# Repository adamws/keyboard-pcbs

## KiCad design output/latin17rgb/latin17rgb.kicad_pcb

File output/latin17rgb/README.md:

## latin17rgb/latin17rgb

[layout](latin17rgb-kle.json) - [PCB](latin17rgb.kicad_pcb)

{:loading="lazy"}

[Open in keyboard-layout-editor](http://www.keyboard-layout-editor.com/##@@=0,0&=0,1&=0,2&=0,3;&@=1,0&=1,1&=1,2&_h:2;&=1,3;&@=2,0&=2,1&=2,2;&@=3,0&=3,1&=3,2&_h:2;&=3,3;&@_w:2;&=4,0&=4,1)

{:loading="lazy"}

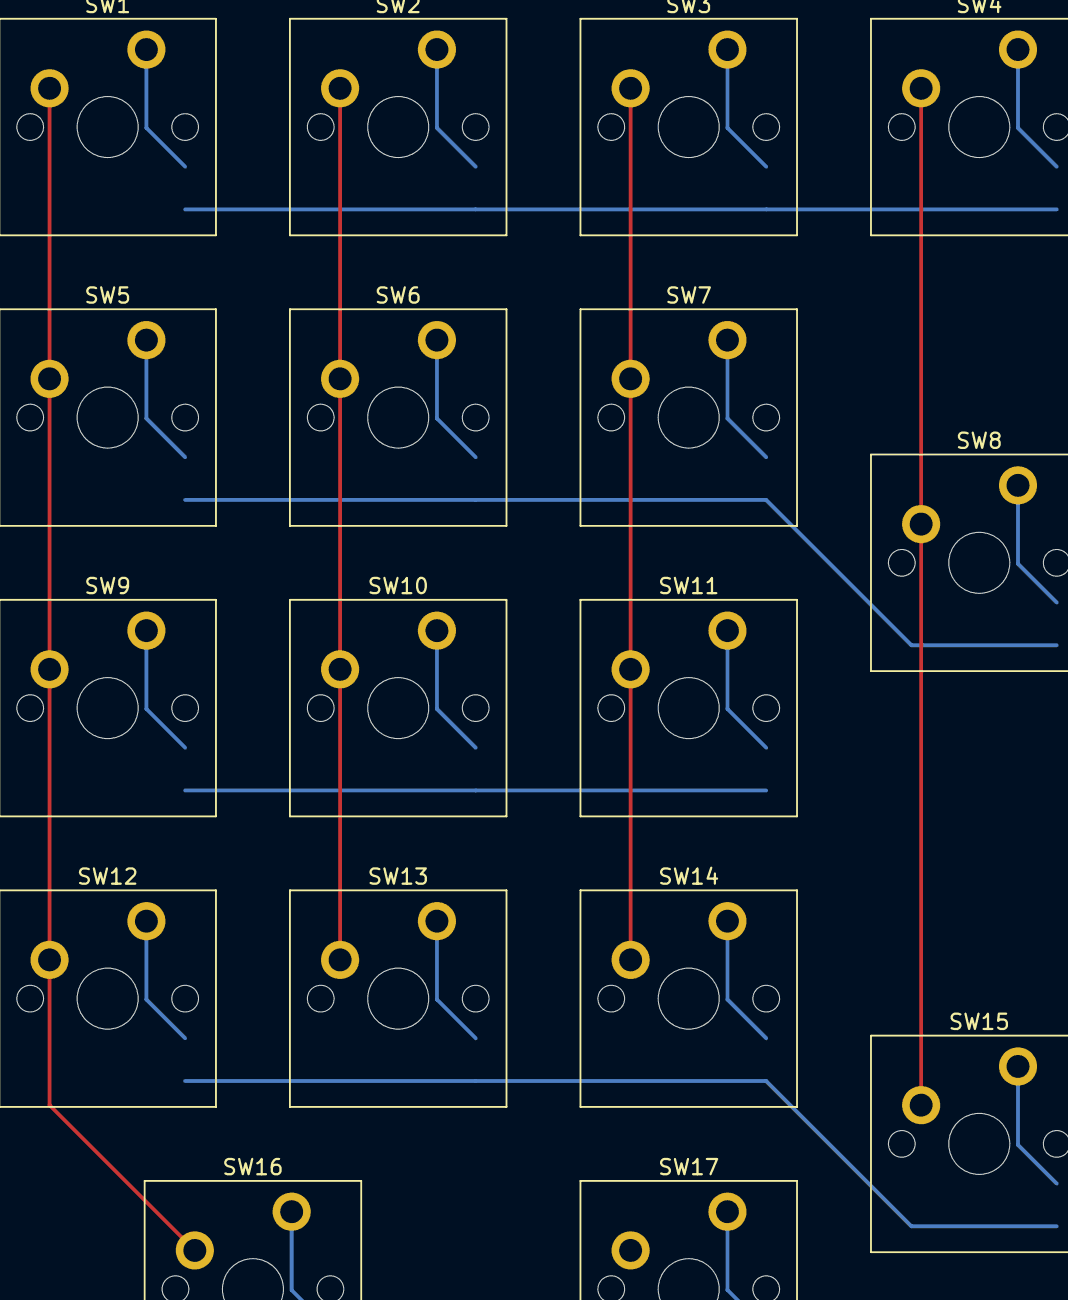
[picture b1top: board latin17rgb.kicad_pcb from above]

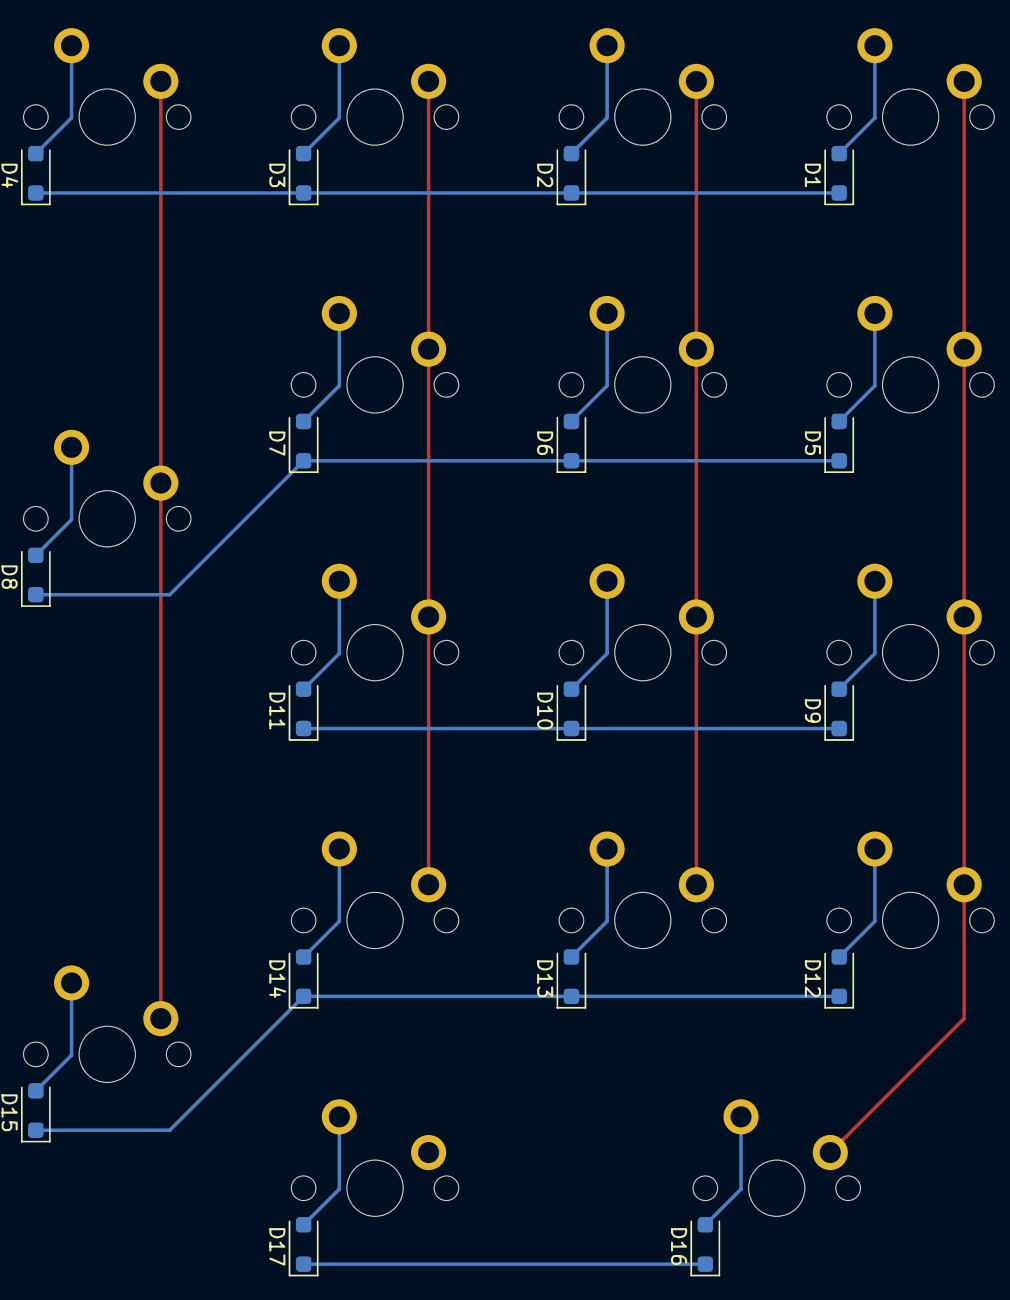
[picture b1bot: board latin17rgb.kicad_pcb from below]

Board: 2 copper layers, 34 parts (17 on the bottom side), 26 nets.

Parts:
D1, D2, D3, D4, D5, D6, D7, D8, D9, D10, D11, D12, D13, D14, D15, D16, D17: D_SOD-123F
SW1, SW2, SW3, SW4, SW5, SW6, SW7, SW8, SW9, SW10, SW11, SW12, SW13, SW14, SW15, SW16, SW17: SW_Cherry_MX_PCB_1.00u

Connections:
COL0: SW1.1, SW5.1, SW9.1, SW12.1, SW16.1
COL1: SW2.1, SW6.1, SW10.1, SW13.1, SW17.1
COL2: SW3.1, SW7.1, SW11.1, SW14.1
COL3: SW4.1, SW8.1, SW15.1
unnamed: D1.2, SW1.2
unnamed: D2.2, SW2.2
unnamed: D3.2, SW3.2
unnamed: D4.2, SW4.2
unnamed: D5.2, SW5.2
unnamed: D6.2, SW6.2
unnamed: D7.2, SW7.2
unnamed: D8.2, SW8.2
unnamed: D9.2, SW9.2
unnamed: D10.2, SW10.2
unnamed: D11.2, SW11.2
unnamed: D12.2, SW12.2
unnamed: D13.2, SW13.2
unnamed: D14.2, SW14.2
unnamed: D15.2, SW15.2
unnamed: D16.2, SW16.2
unnamed: D17.2, SW17.2
ROW0: D1.1, D2.1, D3.1, D4.1
ROW1: D5.1, D6.1, D7.1, D8.1
ROW2: D9.1, D10.1, D11.1
ROW3: D12.1, D13.1, D14.1, D15.1
ROW4: D16.1, D17.1

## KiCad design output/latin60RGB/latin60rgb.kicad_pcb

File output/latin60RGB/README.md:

## latin60RGB/latin60rgb

[layout](latin60rgb-kle.json) - [PCB](latin60rgb.kicad_pcb)

{:loading="lazy"}

[Open in keyboard-layout-editor](http://www.keyboard-layout-editor.com/##@@=0,0&=0,1&=0,2&=0,3&=0,4&=0,5&=0,6&=0,7&=0,8&=0,9&=0,10&=0,11&=0,12&_w:2;&=0,13;&@_w:1.5;&=1,0&=1,1&=1,2&=1,3&=1,4&=1,5&=1,6&=1,7&=1,8&=1,9&=1,10&=1,11&=1,12&_w:1.5;&=1,13;&@_w:1.75;&=2,0&=2,1&=2,2&=2,3&=2,4&=2,5&=2,6&=2,7&=2,8&=2,9&=2,10&=2,11&_w:2.25;&=2,12;&@_w:2;&=3,0&=3,1&=3,2&=3,3&=3,4&=3,5&=3,6&=3,7&=3,8&=3,9&=3,10&=3,11&=3,12&=3,13;&@_x:1.25&w:1.25;&=4,0&_w:1.25;&=4,1&_w:6.25;&=4,2&_w:1.25;&=4,3&_w:1.25;&=4,4)

{:loading="lazy"}

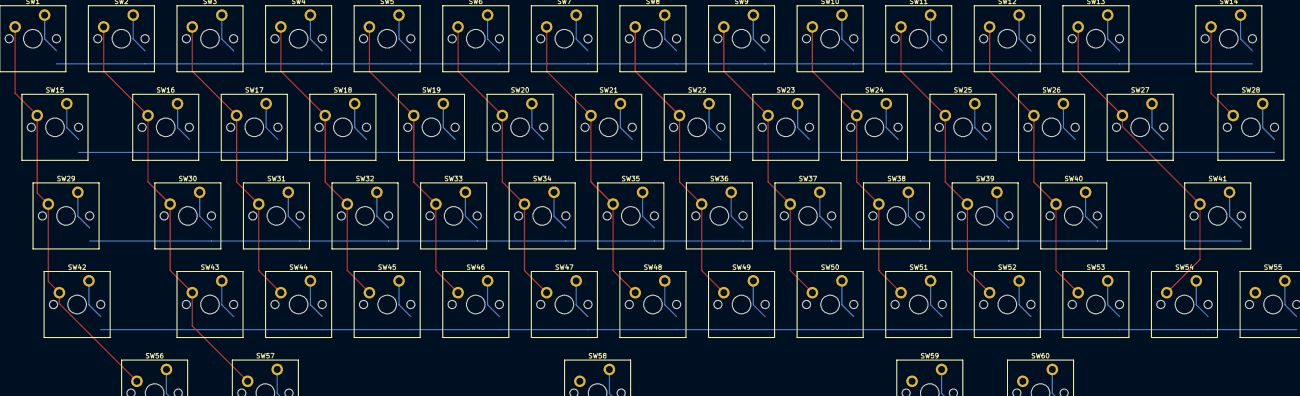
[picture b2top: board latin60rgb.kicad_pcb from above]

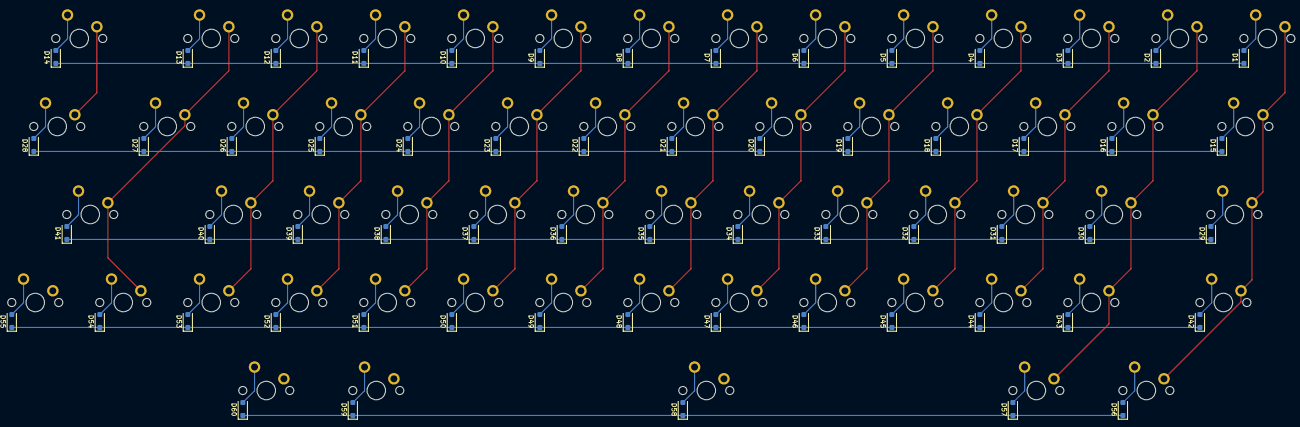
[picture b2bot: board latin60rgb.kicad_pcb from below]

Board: 2 copper layers, 120 parts (60 on the bottom side), 79 nets.

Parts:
D1, D2, D3, D4, D5, D6, D7, D8, D9, D10, D11, D12, D13, D14, D15, D16, D17, D18, D19, D20, D21, D22, D23, D24, D25, D26, D27, D28, D29, D30, D31, D32, D33, D34, D35, D36, D37, D38, D39, D40, D41, D42, D43, D44, D45, D46, D47, D48, D49, D50, D51, D52, D53, D54, D55, D56, D57, D58, D59, D60: D_SOD-123F
SW1, SW2, SW3, SW4, SW5, SW6, SW7, SW8, SW9, SW10, SW11, SW12, SW13, SW14, SW15, SW16, SW17, SW18, SW19, SW20, SW21, SW22, SW23, SW24, SW25, SW26, SW27, SW28, SW29, SW30, SW31, SW32, SW33, SW34, SW35, SW36, SW37, SW38, SW39, SW40, SW41, SW42, SW43, SW44, SW45, SW46, SW47, SW48, SW49, SW50, SW51, SW52, SW53, SW54, SW55, SW56, SW57, SW58, SW59, SW60: SW_Cherry_MX_PCB_1.00u

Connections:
COL0: SW1.1, SW15.1, SW29.1, SW42.1, SW56.1
COL1: SW2.1, SW16.1, SW30.1, SW43.1, SW57.1
COL2: SW3.1, SW17.1, SW31.1, SW44.1, SW58.1
COL3: SW4.1, SW18.1, SW32.1, SW45.1, SW59.1
COL4: SW5.1, SW19.1, SW33.1, SW46.1, SW60.1
COL5: SW6.1, SW20.1, SW34.1, SW47.1
COL6: SW7.1, SW21.1, SW35.1, SW48.1
COL7: SW8.1, SW22.1, SW36.1, SW49.1
COL8: SW9.1, SW23.1, SW37.1, SW50.1
COL9: SW10.1, SW24.1, SW38.1, SW51.1
COL10: SW11.1, SW25.1, SW39.1, SW52.1
COL11: SW12.1, SW26.1, SW40.1, SW53.1
COL12: SW13.1, SW27.1, SW41.1, SW54.1
COL13: SW14.1, SW28.1, SW55.1
unnamed: D1.2, SW1.2
unnamed: D2.2, SW2.2
unnamed: D3.2, SW3.2
unnamed: D4.2, SW4.2
unnamed: D5.2, SW5.2
unnamed: D6.2, SW6.2
unnamed: D7.2, SW7.2
unnamed: D8.2, SW8.2
unnamed: D9.2, SW9.2
unnamed: D10.2, SW10.2
unnamed: D11.2, SW11.2
unnamed: D12.2, SW12.2
unnamed: D13.2, SW13.2
unnamed: D14.2, SW14.2
unnamed: D15.2, SW15.2
unnamed: D16.2, SW16.2
unnamed: D17.2, SW17.2
unnamed: D18.2, SW18.2
unnamed: D19.2, SW19.2
unnamed: D20.2, SW20.2
unnamed: D21.2, SW21.2
unnamed: D22.2, SW22.2
unnamed: D23.2, SW23.2
unnamed: D24.2, SW24.2
unnamed: D25.2, SW25.2
unnamed: D26.2, SW26.2
unnamed: D27.2, SW27.2
unnamed: D28.2, SW28.2
unnamed: D29.2, SW29.2
unnamed: D30.2, SW30.2
unnamed: D31.2, SW31.2
unnamed: D32.2, SW32.2
unnamed: D33.2, SW33.2
unnamed: D34.2, SW34.2
unnamed: D35.2, SW35.2
unnamed: D36.2, SW36.2
unnamed: D37.2, SW37.2
unnamed: D38.2, SW38.2
unnamed: D39.2, SW39.2
unnamed: D40.2, SW40.2
unnamed: D41.2, SW41.2
unnamed: D42.2, SW42.2
unnamed: D43.2, SW43.2
unnamed: D44.2, SW44.2
unnamed: D45.2, SW45.2
unnamed: D46.2, SW46.2
unnamed: D47.2, SW47.2
unnamed: D48.2, SW48.2
unnamed: D49.2, SW49.2
unnamed: D50.2, SW50.2
unnamed: D51.2, SW51.2
unnamed: D52.2, SW52.2
unnamed: D53.2, SW53.2
unnamed: D54.2, SW54.2
unnamed: D55.2, SW55.2
unnamed: D56.2, SW56.2
unnamed: D57.2, SW57.2
unnamed: D58.2, SW58.2
unnamed: D59.2, SW59.2
unnamed: D60.2, SW60.2
ROW0: D1.1, D2.1, D3.1, D4.1, D5.1, D6.1, D7.1, D8.1, D9.1, D10.1, D11.1, D12.1, D13.1, D14.1
ROW1: D15.1, D16.1, D17.1, D18.1, D19.1, D20.1, D21.1, D22.1, D23.1, D24.1, D25.1, D26.1, D27.1, D28.1
ROW2: D29.1, D30.1, D31.1, D32.1, D33.1, D34.1, D35.1, D36.1, D37.1, D38.1, D39.1, D40.1, D41.1
ROW3: D42.1, D43.1, D44.1, D45.1, D46.1, D47.1, D48.1, D49.1, D50.1, D51.1, D52.1, D53.1, D54.1, D55.1
ROW4: D56.1, D57.1, D58.1, D59.1, D60.1

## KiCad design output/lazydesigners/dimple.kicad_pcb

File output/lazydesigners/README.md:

## lazydesigners/bolt

[layout](bolt-kle.json) - [PCB](bolt.kicad_pcb)

{:loading="lazy"}

[Open in keyboard-layout-editor](http://www.keyboard-layout-editor.com/##@@_c=#777777;&=0,0&_c=#cccccc;&=0,1&=0,2&=0,3&=0,4&=0,5&_x:1.5;&=0,6&=0,7&=0,8&=0,9&=0,10&_c=#777777&w:1.75;&=0,11;&@_w:1.25;&=1,0&_c=#aaaaaa;&=1,1&=1,2&=1,3&=1,4&=1,5&_x:1.5;&=1,6&=1,7&=1,8&=1,9&=1,10&_c=#777777&w:1.5;&=1,11;&@_w:1.75;&=2,0&_c=#aaaaaa;&=2,1&=2,2&=2,3&=2,4&=2,5&_x:0.5;&=2,6&=2,7&=2,8&=2,9&=2,10&=2,11&_c=#777777;&=3,11;&@_w:1.25;&=3,0&_w:1.25;&=3,1&_x:0.75&w:1.25;&=3,3&_w:2.25;&=3,4&_x:0.5&w:2.25;&=3,6&=3,7&_x:0.75&c=#cccccc;&=3,8&=3,9&=3,10)

{:loading="lazy"}

## lazydesigners/cassette8

[layout](cassette8-kle.json) - [PCB](cassette8.kicad_pcb)

{:loading="lazy"}

[Open in keyboard-layout-editor](http://www.keyboard-layout-editor.com/##@@=0,0&=0,1&=0,2&=0,3;&@=1,0&=1,1&=1,2&=1,3)

{:loading="lazy"}

## lazydesigners/dimple

[layout](dimple-kle.json) - [PCB](dimple.kicad_pcb)

{:loading="lazy"}

[Open in keyboard-layout-editor](http://www.keyboard-layout-editor.com/##@@_x:1&c=#777777;&=0,0%0A%0A%0A0,0&_c=#cccccc;&=0,1%0A%0A%0A0,0&=0,2%0A%0A%0A0,0&=0,3%0A%0A%0A0,0&=0,4%0A%0A%0A0,0&=0,5%0A%0A%0A0,0&=0,6%0A%0A%0A0,0&=0,7%0A%0A%0A0,0&=0,8%0A%0A%0A0,0&=0,9%0A%0A%0A0,0&=0,10%0A%0A%0A0,0&_c=#aaaaaa&w:1.5;&=0,11%0A%0A%0A0,0;&@_x:1&w:1.25;&=1,0%0A%0A%0A0,0&_c=#cccccc;&=1,1%0A%0A%0A0,0&=1,2%0A%0A%0A0,0&=1,3%0A%0A%0A0,0&=1,4%0A%0A%0A0,0&=1,5%0A%0A%0A0,0&=1,6%0A%0A%0A0,0&=1,7%0A%0A%0A0,0&=1,8%0A%0A%0A0,0&=1,9%0A%0A%0A0,0&=1,10%0A%0A%0A0,0&_c=#aaaaaa&w:1.25;&=1,11%0A%0A%0A0,0;&@_x:1&w:1.75;&=2,0%0A%0A%0A0,0&_c=#cccccc;&=2,1%0A%0A%0A0,0&=2,2%0A%0A%0A0,0&=2,3%0A%0A%0A0,0&=2,4%0A%0A%0A0,0&=2,5%0A%0A%0A0,0&=2,6%0A%0A%0A0,0&=2,7%0A%0A%0A0,0&=2,8%0A%0A%0A0,0&=2,9%0A%0A%0A0,0&_c=#777777&w:1.75;&=2,10%0A%0A%0A0,0;&@_x:1&w:0.75&d:true;&=%0A%0A%0A1,0&_c=#aaaaaa;&=3,0%0A%0A%0A1,0&=3,2%0A%0A%0A1,0&=3,3%0A%0A%0A1,0&_c=#777777&w:2.25;&=3,4%0A%0A%0A1,0&_w:2.75;&=3,6%0A%0A%0A1,0&_c=#aaaaaa;&=3,7%0A%0A%0A1,0&=3,8%0A%0A%0A1,0&=3,9%0A%0A%0A1,0;&@_x:14.5&y:-4&c=#777777;&=0,0%0A%0A%0A0,1&_c=#cccccc;&=0,1%0A%0A%0A0,1&=0,2%0A%0A%0A0,1&=0,3%0A%0A%0A0,1&=0,4%0A%0A%0A0,1&=0,5%0A%0A%0A0,1&=0,6%0A%0A%0A0,1&=0,7%0A%0A%0A0,1&=0,8%0A%0A%0A0,1&=0,9%0A%0A%0A0,1&=0,10%0A%0A%0A0,1&_x:0.25&c=#777777&w:1.25&h:2&w2:1.5&h2:1&x2:-0.25;&=1,11%0A%0A%0A0,1&_x:1.0&w:1.25;&=0,0%0A%0A%0A0,2&_c=#cccccc;&=0,1%0A%0A%0A0,2&=0,2%0A%0A%0A0,2&=0,3%0A%0A%0A0,2&=0,4%0A%0A%0A0,2&=0,5%0A%0A%0A0,2&=0,6%0A%0A%0A0,2&=0,7%0A%0A%0A0,2&=0,8%0A%0A%0A0,2&=0,9%0A%0A%0A0,2&=0,10%0A%0A%0A0,2&_c=#aaaaaa&w:1.25;&=0,11%0A%0A%0A0,2;&@_x:14.5&w:1.25;&=1,0%0A%0A%0A0,1&_c=#cccccc;&=1,1%0A%0A%0A0,1&=1,2%0A%0A%0A0,1&=1,3%0A%0A%0A0,1&=1,4%0A%0A%0A0,1&=1,5%0A%0A%0A0,1&=1,6%0A%0A%0A0,1&=1,7%0A%0A%0A0,1&=1,8%0A%0A%0A0,1&=1,9%0A%0A%0A0,1&=1,10%0A%0A%0A0,1&_x:2.25&w:1.25;&=1,0%0A%0A%0A0,2&=1,1%0A%0A%0A0,2&=1,2%0A%0A%0A0,2&=1,3%0A%0A%0A0,2&=1,4%0A%0A%0A0,2&=1,5%0A%0A%0A0,2&=1,6%0A%0A%0A0,2&=1,7%0A%0A%0A0,2&=1,8%0A%0A%0A0,2&=1,9%0A%0A%0A0,2&=1,10%0A%0A%0A0,2&_c=#aaaaaa&w:1.25;&=1,11%0A%0A%0A0,2;&@_x:14.5&c=#777777&w:1.75;&=2,0%0A%0A%0A0,1&_c=#cccccc;&=2,1%0A%0A%0A0,1&=2,2%0A%0A%0A0,1&=2,3%0A%0A%0A0,1&=2,4%0A%0A%0A0,1&=2,5%0A%0A%0A0,1&=2,6%0A%0A%0A0,1&=2,7%0A%0A%0A0,1&=2,8%0A%0A%0A0,1&=2,9%0A%0A%0A0,1&_c=#777777&w:1.75;&=2,10%0A%0A%0A0,1&_x:1.0&w:1.25;&=2,0%0A%0A%0A0,2&_c=#cccccc;&=2,1%0A%0A%0A0,2&=2,2%0A%0A%0A0,2&=2,3%0A%0A%0A0,2&=2,4%0A%0A%0A0,2&=2,5%0A%0A%0A0,2&=2,6%0A%0A%0A0,2&=2,7%0A%0A%0A0,2&=2,8%0A%0A%0A0,2&=2,9%0A%0A%0A0,2&=2,10%0A%0A%0A0,2&_c=#777777&w:1.25;&=2,11%0A%0A%0A0,2;&@_x:13.75&c=#aaaaaa&w:0.75&d:true;&=%0A%0A%0A1,1&=3,0%0A%0A%0A1,1&=3,2%0A%0A%0A1,1&=3,3%0A%0A%0A1,1&=3,4%0A%0A%0A1,1&_c=#777777&w:3;&=3,5%0A%0A%0A1,1&_c=#aaaaaa;&=3,6%0A%0A%0A1,1&=3,7%0A%0A%0A1,1&=3,8%0A%0A%0A1,1&=3,9%0A%0A%0A1,1&_x:1.0&w:0.75&d:true;&=%0A%0A%0A1,2&=3,0%0A%0A%0A1,2&=3,2%0A%0A%0A1,2&=3,3%0A%0A%0A1,2&_c=#777777&w:2;&=3,4%0A%0A%0A1,2&_c=#aaaaaa;&=3,5%0A%0A%0A1,2&_c=#777777&w:2;&=3,6%0A%0A%0A1,2&_c=#aaaaaa;&=3,7%0A%0A%0A1,2&=3,8%0A%0A%0A1,2&=3,9%0A%0A%0A1,2&_x:1.0&w:0.75&d:true;&=%0A%0A%0A1,3&=3,0%0A%0A%0A1,3&=3,2%0A%0A%0A1,3&_c=#777777&w:7;&=3,4%0A%0A%0A1,3&_c=#aaaaaa;&=3,8%0A%0A%0A1,3&=3,9%0A%0A%0A1,3&_x:1.0&w:1.25;&=3,0%0A%0A%0A1,4&_x:0.63&w:1.25;&=3,2%0A%0A%0A1,4&=3,3%0A%0A%0A1,4&_c=#777777&w:2;&=3,4%0A%0A%0A1,4&_w:2.25;&=3,6%0A%0A%0A1,4&_c=#aaaaaa;&=3,7%0A%0A%0A1,4&_w:1.25;&=3,8%0A%0A%0A1,4&_x:0.63&w:1.25;&=3,9%0A%0A%0A1,4&_x:1.0&w:1.25;&=3,0%0A%0A%0A1,5&_x:0.63&w:1.25;&=3,2%0A%0A%0A1,5&_c=#777777&w:6.25;&=3,4%0A%0A%0A1,5&_c=#aaaaaa&w:1.25;&=3,8%0A%0A%0A1,5&_x:0.63&w:1.25;&=3,9%0A%0A%0A1,5)

{:loading="lazy"}

## lazydesigners/dimpleplus

[layout](dimpleplus-kle.json) - [PCB](dimpleplus.kicad_pcb)

{:loading="lazy"}

[Open in keyboard-layout-editor](http://www.keyboard-layout-editor.com/##@@_c=#777777;&=0,0&_x:0.5&c=#cccccc;&=0,1&=0,2&=0,3&=0,4&=0,5&=0,6&=0,7&=0,8&=0,9&=0,10%0A%0A%0A0,0&=0,11%0A%0A%0A0,0;&@_y:0.25&c=#aaaaaa;&=1,0&=1,1&=1,2&=1,3&=1,4&=1,5&=1,6&=1,7&=1,8&=1,9&=1,10&_c=#777777&w:1.5;&=1,11%0A%0A%0A1,0;&@_w:1.25;&=2,0&_c=#aaaaaa;&=2,1&=2,2&=2,3&=2,4&=2,5&=2,6&=2,7&=2,8&=2,9&=2,10%0A%0A%0A1,0&_c=#777777&w:1.25;&=2,11%0A%0A%0A1,0;&@_w:1.75;&=3,0&_c=#cccccc;&=3,1&=3,2&=3,3&=3,4&=3,5&=3,6&=3,7&=3,8&=3,9&_c=#777777&w:1.75;&=3,10;&@_x:0.75;&=4,0&=4,2&=4,3%0A%0A%0A2,0&_w:2.25;&=4,4%0A%0A%0A2,0&_w:2.75;&=4,6%0A%0A%0A2,0&=4,7%0A%0A%0A2,0&=4,8&=4,9;&@_x:12.5&y:-5.25&w:2;&=0,10%0A%0A%0A0,1;&@_x:12.5&y:0.25&w:1.5;&=1,11%0A%0A%0A1,1&_x:1.75&w:1.25&h:2&w2:1.5&h2:1&x2:-0.25;&=1,11%0A%0A%0A1,2;&@_x:11.75&w:2.25;&=2,11%0A%0A%0A1,1&_x:0.75&c=#cccccc;&=2,10%0A%0A%0A1,2;&@_x:9.75&y:1.0&c=#777777&w:7;&=4,4%0A%0A%0A2,1)

{:loading="lazy"}

## lazydesigners/the30

[layout](the30-kle.json) - [PCB](the30.kicad_pcb)

{:loading="lazy"}

[Open in keyboard-layout-editor](http://www.keyboard-layout-editor.com/##@@=0,0&=0,1&=0,2&=0,3&=0,4&=0,5&=0,6&=0,7&=0,8&=0,9;&@=1,0&=1,1&=1,2&=1,3&=1,4&=1,5&=1,6&=1,7&=1,8&=1,9;&@=2,0&=2,1&=2,2&=2,3&=2,4&=2,5&=2,6&=2,7&=2,8&=2,9)

{:loading="lazy"}

## lazydesigners/the40

[layout](the40-kle.json) - [PCB](the40.kicad_pcb)

{:loading="lazy"}

[Open in keyboard-layout-editor](http://www.keyboard-layout-editor.com/##@@_c=#aaaaaa;&=0,0&_c=#cccccc;&=0,1&=0,2&=0,3&=0,4&=0,5&=0,6&=0,7&=0,8&=0,9&=0,10&_c=#aaaaaa;&=0,11;&@_w:1.25;&=1,0%0A%0A%0A0,0&_c=#cccccc;&=1,1%0A%0A%0A0,0&=1,2%0A%0A%0A0,0&=1,3%0A%0A%0A0,0&=1,4%0A%0A%0A0,0&=1,5%0A%0A%0A0,0&=1,6%0A%0A%0A0,0&=1,7%0A%0A%0A0,0&=1,8%0A%0A%0A0,0&=1,9%0A%0A%0A0,0&_c=#777777&w:1.75;&=1,10%0A%0A%0A0,0;&@_c=#aaaaaa&w:1.75;&=2,0%0A%0A%0A0,0&_c=#cccccc;&=2,1%0A%0A%0A0,0&=2,2%0A%0A%0A0,0&=2,3%0A%0A%0A0,0&=2,4%0A%0A%0A0,0&=2,5%0A%0A%0A0,0&=2,6%0A%0A%0A0,0&=2,7%0A%0A%0A0,0&=2,8%0A%0A%0A0,0&_w:1.25;&=2,9%0A%0A%0A0,0&_c=#aaaaaa;&=2,10%0A%0A%0A0,0;&@_w:1.25;&=3,0%0A%0A%0A1,0&=3,1%0A%0A%0A1,0&_w:1.25;&=3,2%0A%0A%0A1,0&_c=#cccccc&w:2.25;&=3,4%0A%0A%0A1,0&_w:2.75;&=3,6%0A%0A%0A1,0&_c=#aaaaaa&w:1.25;&=3,8%0A%0A%0A1,0&=3,9%0A%0A%0A1,0&_w:1.25;&=3,10%0A%0A%0A1,0;&@_x:12.0&y:-3&w:1.25;&=1,0%0A%0A%0A0,1&_c=#cccccc;&=1,1%0A%0A%0A0,1&=1,2%0A%0A%0A0,1&=1,3%0A%0A%0A0,1&=1,4%0A%0A%0A0,1&=1,5%0A%0A%0A0,1&=1,6%0A%0A%0A0,1&=1,7%0A%0A%0A0,1&=1,8%0A%0A%0A0,1&=1,9%0A%0A%0A0,1&_c=#777777&w:1.75;&=1,10%0A%0A%0A0,1&=1,0%0A%0A%0A0,2&_c=#cccccc;&=1,1%0A%0A%0A0,2&=1,2%0A%0A%0A0,2&=1,3%0A%0A%0A0,2&=1,4%0A%0A%0A0,2&=1,5%0A%0A%0A0,2&=1,6%0A%0A%0A0,2&=1,7%0A%0A%0A0,2&=1,8%0A%0A%0A0,2&=1,9%0A%0A%0A0,2&=1,10%0A%0A%0A0,2&_c=#aaaaaa;&=1,11%0A%0A%0A0,2;&@_x:12.0&w:1.75;&=2,0%0A%0A%0A0,1&_c=#cccccc;&=2,1%0A%0A%0A0,1&=2,2%0A%0A%0A0,1&=2,3%0A%0A%0A0,1&=2,4%0A%0A%0A0,1&=2,5%0A%0A%0A0,1&=2,6%0A%0A%0A0,1&=2,7%0A%0A%0A0,1&=2,8%0A%0A%0A0,1&=2,9%0A%0A%0A0,1&_c=#aaaaaa&w:1.25;&=2,10%0A%0A%0A0,1&=2,0%0A%0A%0A0,2&_c=#cccccc;&=2,1%0A%0A%0A0,2&=2,2%0A%0A%0A0,2&=2,3%0A%0A%0A0,2&=2,4%0A%0A%0A0,2&=2,5%0A%0A%0A0,2&=2,6%0A%0A%0A0,2&=2,7%0A%0A%0A0,2&=2,8%0A%0A%0A0,2&=2,9%0A%0A%0A0,2&=2,10%0A%0A%0A0,2&_c=#aaaaaa;&=2,11%0A%0A%0A0,2;&@_x:12.0&w:1.25;&=3,0%0A%0A%0A1,1&=3,1%0A%0A%0A1,1&=3,2%0A%0A%0A1,1&_c=#cccccc&w:6.25;&=3,4%0A%0A%0A1,1&_c=#aaaaaa&w:1.25;&=3,9%0A%0A%0A1,1&_w:1.25;&=3,10%0A%0A%0A1,1&=3,0%0A%0A%0A1,2&=3,1%0A%0A%0A1,2&=3,2%0A%0A%0A1,2&=3,3%0A%0A%0A1,2&=3,4%0A%0A%0A1,2&=3,5%0A%0A%0A1,2&=3,6%0A%0A%0A1,2&=3,7%0A%0A%0A1,2&=3,8%0A%0A%0A1,2&=3,9%0A%0A%0A1,2&=3,10%0A%0A%0A1,2&=3,11%0A%0A%0A1,2&=3,0%0A%0A%0A1,3&=3,1%0A%0A%0A1,3&=3,2%0A%0A%0A1,3&=3,3%0A%0A%0A1,3&=3,4%0A%0A%0A1,3&_c=#cccccc&w:2;&=3,5%0A%0A%0A1,3&_c=#aaaaaa;&=3,7%0A%0A%0A1,3&=3,8%0A%0A%0A1,3&=3,9%0A%0A%0A1,3&=3,10%0A%0A%0A1,3&=3,11%0A%0A%0A1,3)

{:loading="lazy"}

## lazydesigners/the60rev2

[layout](the60rev2-kle.json) - [PCB](the60rev2.kicad_pcb)

{:loading="lazy"}

[Open in keyboard-layout-editor](http://www.keyboard-layout-editor.com/##@@_x:2.5&c=#777777;&=0,0&_c=#cccccc;&=0,1&=0,2&=0,3&=0,4&=0,5&=0,6&=0,7&=0,8&=0,9&=0,10&=0,11&=0,12&_c=#aaaaaa&w:2;&=0,13%0A%0A%0A0,0;&@_x:2.5&w:1.5;&=1,0&_c=#cccccc;&=1,1&=1,2&=1,3&=1,4&=1,5&=1,6&=1,7&=1,8&=1,9&=1,10&=1,11&=1,12&_c=#aaaaaa&w:1.5;&=1,13%0A%0A%0A1,0;&@_x:2.5&w:1.75;&=2,0&_c=#cccccc;&=2,1&=2,2&=2,3&=2,4&=2,5&=2,6&=2,7&=2,8&=2,9&=2,10&=2,11&_c=#777777&w:2.25;&=2,13%0A%0A%0A1,0;&@_x:2.5&c=#aaaaaa&w:2.25;&=3,0%0A%0A%0A2,0&_c=#cccccc;&=3,2&=3,3&=3,4&=3,5&=3,6&=3,7&=3,8&=3,9&=3,10&=3,11&_c=#aaaaaa&w:1.75;&=3,12%0A%0A%0A3,0&=3,13%0A%0A%0A3,0;&@_x:2.5&w:1.5;&=4,0%0A%0A%0A4,0&=4,1%0A%0A%0A4,0&_w:1.5;&=4,2%0A%0A%0A4,0&_c=#cccccc&w:7;&=4,6%0A%0A%0A4,0&_c=#aaaaaa&w:1.5;&=4,11%0A%0A%0A4,0&=4,12%0A%0A%0A4,0&_w:1.5;&=4,13%0A%0A%0A4,0;&@_x:18.5&y:-5&c=#cccccc;&=0,13%0A%0A%0A0,1&=2,12%0A%0A%0A0,1;&@_x:19.25&c=#777777&w:1.25&h:2&w2:1.5&h2:1&x2:-0.25;&=2,13%0A%0A%0A1,1;&@_x:18.25&c=#cccccc;&=1,13%0A%0A%0A1,1;&@_c=#aaaaaa&w:1.25;&=3,0%0A%0A%0A2,1&=3,1%0A%0A%0A2,1&_x:15.5&w:2.75;&=3,13%0A%0A%0A3,1;&@_x:2.5&y:1&w:1.5;&=4,0%0A%0A%0A4,1&=4,1%0A%0A%0A4,1&_w:1.5;&=4,2%0A%0A%0A4,1&_c=#cccccc&w:2.25;&=4,4%0A%0A%0A4,1&=4,6%0A%0A%0A4,1&_w:2.75;&=4,8%0A%0A%0A4,1&_c=#aaaaaa;&=4,10%0A%0A%0A4,1&_w:1.5;&=4,11%0A%0A%0A4,1&=4,12%0A%0A%0A4,1&_w:1.5;&=4,13%0A%0A%0A4,1;&@_x:2.5&y:0.25&w:1.5;&=4,0%0A%0A%0A4,2&_d:true;&=%0A%0A%0A4,2&_w:1.5;&=4,2%0A%0A%0A4,2&_c=#cccccc&w:7;&=4,6%0A%0A%0A4,2&_c=#aaaaaa&w:1.5;&=4,11%0A%0A%0A4,2&_d:true;&=%0A%0A%0A4,2&_w:1.5;&=4,13%0A%0A%0A4,2;&@_x:2.5&w:1.5&d:true;&=%0A%0A%0A4,3&=4,1%0A%0A%0A4,3&_w:1.5;&=4,2%0A%0A%0A4,3&_c=#cccccc&w:7;&=4,6%0A%0A%0A4,3&_c=#aaaaaa&w:1.5;&=4,11%0A%0A%0A4,3&=4,12%0A%0A%0A4,3&_w:1.5&d:true;&=%0A%0A%0A4,3;&@_x:2.5&y:0.25&w:1.5;&=4,0%0A%0A%0A4,4&_d:true;&=%0A%0A%0A4,4&_w:1.5;&=4,2%0A%0A%0A4,4&_c=#cccccc&w:2.25;&=4,4%0A%0A%0A4,4&=4,6%0A%0A%0A4,4&_w:2.75;&=4,8%0A%0A%0A4,4&_c=#aaaaaa;&=4,10%0A%0A%0A4,4&_w:1.5;&=4,11%0A%0A%0A4,4&_d:true;&=%0A%0A%0A4,4&_w:1.5;&=4,13%0A%0A%0A4,4;&@_x:2.5&w:1.5&d:true;&=%0A%0A%0A4,5&=4,1%0A%0A%0A4,5&_w:1.5;&=4,2%0A%0A%0A4,5&_c=#cccccc&w:2.25;&=4,4%0A%0A%0A4,5&=4,6%0A%0A%0A4,5&_w:2.75;&=4,8%0A%0A%0A4,5&_c=#aaaaaa;&=4,10%0A%0A%0A4,5&_w:1.5;&=4,11%0A%0A%0A4,5&=4,12%0A%0A%0A4,5&_w:1.5&d:true;&=%0A%0A%0A4,5)

{:loading="lazy"}

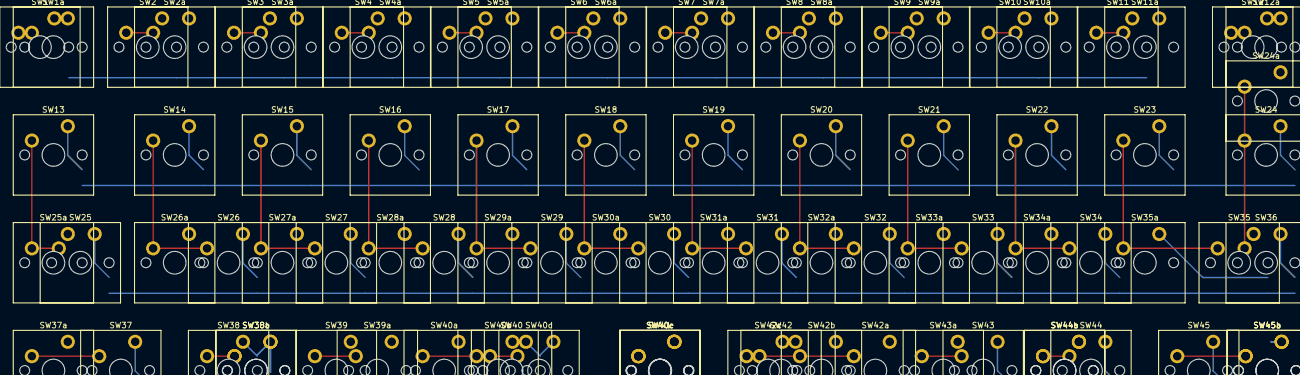
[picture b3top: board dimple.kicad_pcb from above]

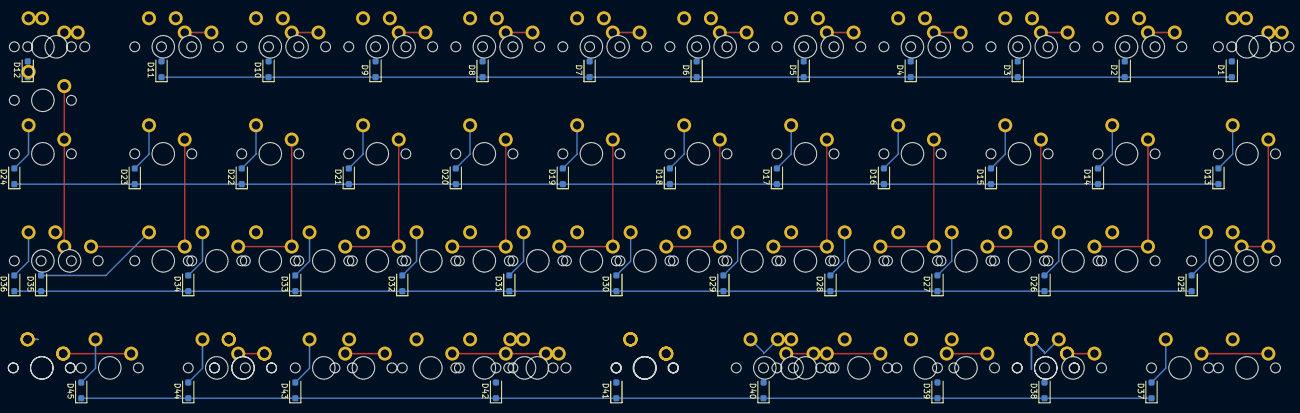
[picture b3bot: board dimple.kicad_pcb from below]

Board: 2 copper layers, 131 parts (45 on the bottom side), 61 nets.

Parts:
D1, D2, D3, D4, D5, D6, D7, D8, D9, D10, D11, D12, D13, D14, D15, D16, D17, D18, D19, D20, D21, D22, D23, D24, D25, D26, D27, D28, D29, D30, D31, D32, D33, D34, D35, D36, D37, D38, D39, D40, D41, D42, D43, D44, D45: D_SOD-123F
SW1, SW1a, SW2, SW2a, SW3, SW3a, SW4, SW4a, SW5, SW5a, SW6, SW6a, SW7, SW7a, SW8, SW8a, SW9, SW9a, SW10, SW10a, SW11, SW11a, SW12, SW12a, SW13, SW14, SW15, SW16, SW17, SW18, SW19, SW20, SW21, SW22, SW23, SW24, SW24a, SW25, SW25a, SW26, SW26a, SW27, SW27a, SW28, SW28a, SW29, SW29a, SW30, SW30a, SW31, SW31a, SW32, SW32a, SW33, SW33a, SW34, SW34a, SW35, SW35a, SW36, SW37, SW37a, SW38, SW38a, SW38b, SW39, SW39a, SW40, SW40a, SW40b, SW40c, SW40d, SW40e, SW41, SW42, SW42a, SW42b, SW42c, SW43, SW43a, SW44, SW44a, SW44b, SW45, SW45a, SW45b: SW_Cherry_MX_PCB_1.00u

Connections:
COL0: SW1.1, SW1a.1, SW13.1, SW25.1, SW25a.1, SW37.1, SW37a.1
COL1: SW2.1, SW2a.1, SW14.1, SW26.1, SW26a.1
COL2: SW3.1, SW3a.1, SW15.1, SW27.1, SW27a.1, SW38.1, SW38a.1, SW38b.1
COL3: SW4.1, SW4a.1, SW16.1, SW28.1, SW28a.1, SW39.1, SW39a.1
COL4: SW5.1, SW5a.1, SW17.1, SW29.1, SW29a.1, SW40.1, SW40a.1, SW40b.1, SW40c.1, SW40d.1, SW40e.1
COL5: SW6.1, SW6a.1, SW18.1, SW30.1, SW30a.1, SW41.1
COL6: SW7.1, SW7a.1, SW19.1, SW31.1, SW31a.1, SW42.1, SW42a.1, SW42b.1, SW42c.1
COL7: SW8.1, SW8a.1, SW20.1, SW32.1, SW32a.1, SW43.1, SW43a.1
COL8: SW9.1, SW9a.1, SW21.1, SW33.1, SW33a.1, SW44.1, SW44a.1, SW44b.1
COL9: SW10.1, SW10a.1, SW22.1, SW34.1, SW34a.1, SW45.1, SW45a.1, SW45b.1
COL10: SW11.1, SW11a.1, SW23.1, SW35.1, SW35a.1
COL11: SW12.1, SW12a.1, SW24.1, SW24a.1, SW36.1
unnamed: D1.2, SW1.2, SW1a.2
unnamed: D2.2, SW2.2, SW2a.2
unnamed: D3.2, SW3.2, SW3a.2
unnamed: D4.2, SW4.2, SW4a.2
unnamed: D5.2, SW5.2, SW5a.2
unnamed: D6.2, SW6.2, SW6a.2
unnamed: D7.2, SW7.2, SW7a.2
unnamed: D8.2, SW8.2, SW8a.2
unnamed: D9.2, SW9.2, SW9a.2
unnamed: D10.2, SW10.2, SW10a.2
unnamed: D11.2, SW11.2, SW11a.2
unnamed: D12.2, SW12.2, SW12a.2
unnamed: D13.2, SW13.2
unnamed: D14.2, SW14.2
unnamed: D15.2, SW15.2
unnamed: D16.2, SW16.2
unnamed: D17.2, SW17.2
unnamed: D18.2, SW18.2
unnamed: D19.2, SW19.2
unnamed: D20.2, SW20.2
unnamed: D21.2, SW21.2
unnamed: D22.2, SW22.2
unnamed: D23.2, SW23.2
unnamed: D24.2, SW24.2, SW24a.2
unnamed: D25.2, SW25.2, SW25a.2
unnamed: D26.2, SW26.2, SW26a.2
unnamed: D27.2, SW27.2, SW27a.2
unnamed: D28.2, SW28.2, SW28a.2
unnamed: D29.2, SW29.2, SW29a.2
unnamed: D30.2, SW30.2, SW30a.2
unnamed: D31.2, SW31.2, SW31a.2
unnamed: D32.2, SW32.2, SW32a.2
unnamed: D33.2, SW33.2, SW33a.2
unnamed: D34.2, SW34.2, SW34a.2
unnamed: D35.2, SW35.2, SW35a.2
unnamed: D36.2, SW36.2
unnamed: D37.2, SW37.2, SW37a.2
unnamed: D38.2, SW38.2, SW38a.2, SW38b.2
unnamed: D39.2, SW39.2, SW39a.2
unnamed: D40.2, SW40.2, SW40a.2, SW40b.2, SW40c.2, SW40d.2, SW40e.2
unnamed: D41.2, SW41.2
unnamed: D42.2, SW42.2, SW42a.2, SW42b.2, SW42c.2
unnamed: D43.2, SW43.2, SW43a.2
unnamed: D44.2, SW44.2, SW44a.2, SW44b.2
unnamed: D45.2, SW45.2, SW45a.2, SW45b.2
ROW0: D1.1, D2.1, D3.1, D4.1, D5.1, D6.1, D7.1, D8.1, D9.1, D10.1, D11.1, D12.1
ROW1: D13.1, D14.1, D15.1, D16.1, D17.1, D18.1, D19.1, D20.1, D21.1, D22.1, D23.1, D24.1
ROW2: D25.1, D26.1, D27.1, D28.1, D29.1, D30.1, D31.1, D32.1, D33.1, D34.1, D35.1, D36.1
ROW3: D37.1, D38.1, D39.1, D40.1, D41.1, D42.1, D43.1, D44.1, D45.1
